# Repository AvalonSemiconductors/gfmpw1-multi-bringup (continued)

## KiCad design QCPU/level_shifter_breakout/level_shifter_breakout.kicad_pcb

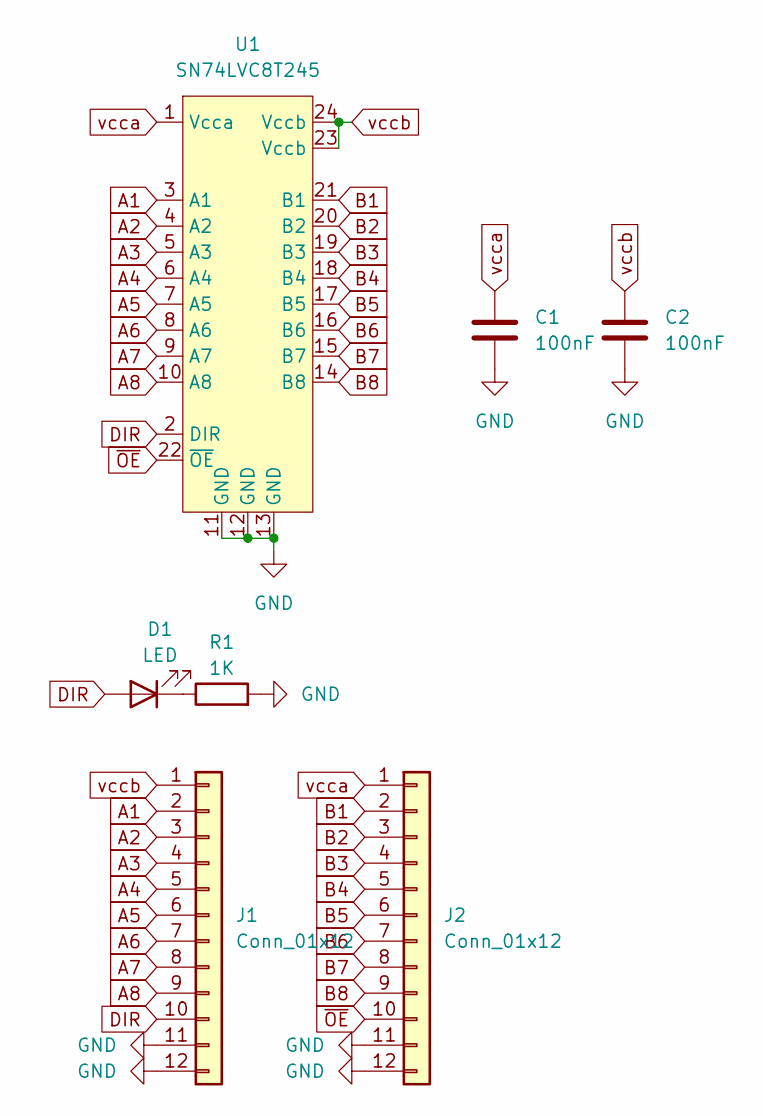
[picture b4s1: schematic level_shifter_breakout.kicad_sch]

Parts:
C1, C2: 100nF; C_0805_2012Metric_Pad1.18x1.45mm_HandSolder
D1: LED; LED_1206_3216Metric_Pad1.42x1.75mm_HandSolder
J1, J2: Conn_01x12; PinHeader_1x12_P2.54mm_Vertical
R1: 1K; R_2010_5025Metric_Pad1.40x2.65mm_HandSolder
U1: SN74LVC8T245; TSSOP-24_4.4x7.8mm_P0.65mm

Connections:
A1: J1.2, U1.3 (A1)
A2: J1.3, U1.4 (A2)
A3: J1.4, U1.5 (A3)
A4: J1.5, U1.6 (A4)
A5: J1.6, U1.7 (A5)
A6: J1.7, U1.8 (A6)
A7: J1.8, U1.9 (A7)
A8: J1.9, U1.10 (A8)
B1: J2.2, U1.21 (B1)
B2: J2.3, U1.20 (B2)
B3: J2.4, U1.19 (B3)
B4: J2.5, U1.18 (B4)
B5: J2.6, U1.17 (B5)
B6: J2.7, U1.16 (B6)
B7: J2.8, U1.15 (B7)
B8: J2.9, U1.14 (B8)
DIR: D1.2 (A), J1.10, U1.2 (DIR)
GND: C1.2, C2.2, J1.11, J1.12, J2.11, J2.12, R1.2, U1.11 (GND), U1.12 (GND), U1.13 (GND)
unnamed: D1.1 (K), R1.1
vcca: C1.1, J2.1, U1.1 (Vcca)
vccb: C2.1, J1.1, U1.23 (Vccb), U1.24 (Vccb)
~OE: J2.10, U1.22 (~OE)

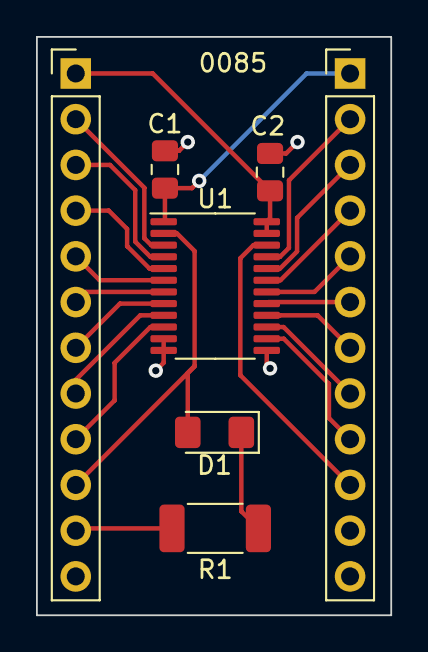
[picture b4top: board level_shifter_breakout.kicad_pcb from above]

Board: 2 copper layers, 19.7 x 32.1 mm, 7 parts (0 on the bottom side), 22 nets.

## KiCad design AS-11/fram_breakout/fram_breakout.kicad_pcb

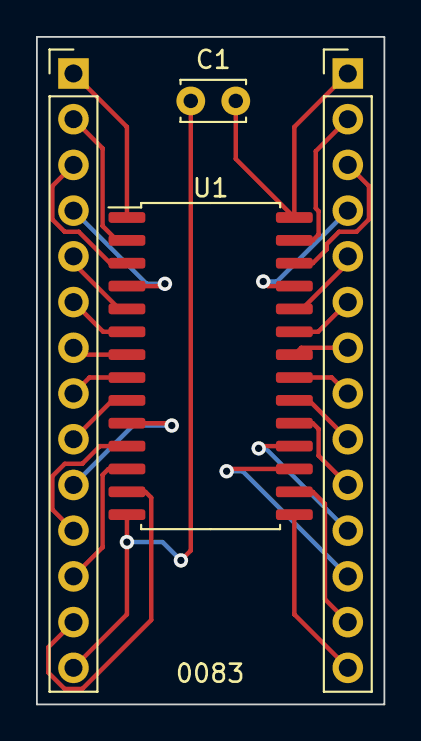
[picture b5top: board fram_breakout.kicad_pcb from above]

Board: 2 copper layers, 19.3 x 37.1 mm, 4 parts (0 on the bottom side), 28 nets.

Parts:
C1: 100nF; C_Disc_D3.4mm_W2.1mm_P2.50mm
J1, J2: Conn_01x14; PinHeader_1x14_P2.54mm_Vertical
U1: FM18W08-SG; SOIC-28W_7.5x17.9mm_P1.27mm

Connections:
A0: J2.10, U1.10 (A0)
A1: J2.9, U1.9 (A1)
A2: J2.8, U1.8 (A2)
A3: J2.7, U1.7 (A3)
A4: J2.6, U1.6 (A4)
A5: J2.5, U1.5 (A5)
A6: J2.4, U1.4 (A6)
A7: J2.3, U1.3 (A7)
A8: J1.4, U1.25 (A8)
A9: J1.5, U1.24 (A9)
A10: J1.8, U1.21 (A10)
A11: J1.6, U1.23 (A11)
A12: J2.2, U1.2 (A12)
A13: J1.3, U1.26 (A13)
A14: J2.1, U1.1 (A14)
DQ0: J2.11, U1.11 (DQ0)
DQ1: J2.12, U1.12 (DQ1)
DQ2: J2.13, U1.13 (DQ2)
DQ3: J1.14, U1.15 (DQ3)
DQ4: J1.13, U1.16 (DQ4)
DQ5: J1.12, U1.17 (DQ5)
DQ6: J1.11, U1.18 (DQ6)
DQ7: J1.10, U1.19 (DQ7)
unnamed: C1.2, J1.1, U1.28 (VDD)
unnamed: C1.1, J2.14, U1.14 (VSS)
~CE: J1.9, U1.20 (~CE)
~OE: J1.7, U1.22 (~OE)
~WE: J1.2, U1.27 (~WE)

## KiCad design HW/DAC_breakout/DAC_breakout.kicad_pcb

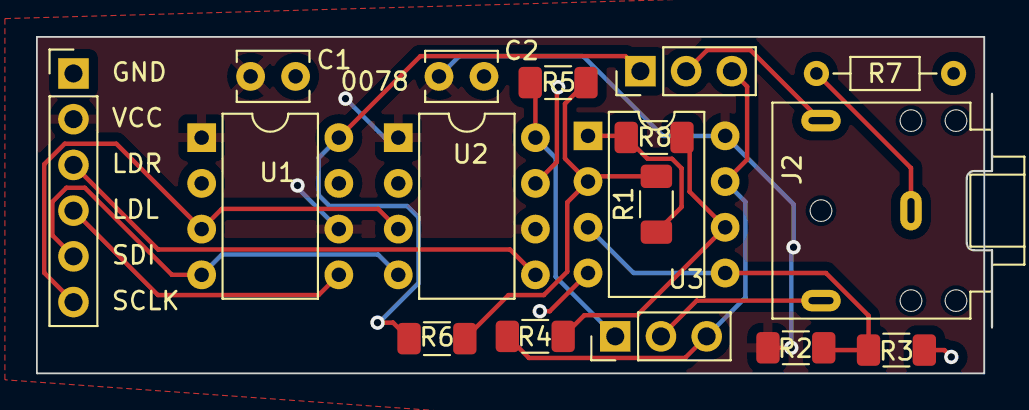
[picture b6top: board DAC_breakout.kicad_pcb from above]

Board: 2 copper layers, 53.1 x 18.7 mm, 17 parts (0 on the bottom side), 16 nets.

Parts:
C1, C2: 100nF; C_Disc_D3.8mm_W2.6mm_P2.50mm
J1: Conn_01x06; PinHeader_1x06_P2.54mm_Vertical
J2: AudioJack3; Jack_3.5mm_CUI_SJ1-3523N_Horizontal
J3, J4: Conn_01x03; PinHeader_1x03_P2.54mm_Vertical
R1, R2, R3, R4, R5, R6, R8: 10K; R_1206_3216Metric_Pad1.30x1.75mm_HandSolder
R7: 1K; R_Axial_DIN0204_L3.6mm_D1.6mm_P7.62mm_Horizontal
U1, U2: DAC7611; DIP-8_W7.62mm
U3: LM358; DIP-8_W7.62mm

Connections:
GND: C1.2, C2.2, J1.1, R3.2, R7.2, U1.2 (~CS), U1.7 (GND), U2.2 (~CS), U2.7 (GND), U3.4 (V-)
unnamed: J1.3, U2.5 (~LD)
unnamed: J1.4, U1.5 (~LD)
unnamed: J1.5, U1.4 (SDI), U2.4 (SDI)
unnamed: J1.6, U1.3 (CLK), U2.3 (CLK)
unnamed: J2.S, R7.1
unnamed: J3.1, R6.2, U1.8 (Vout)
unnamed: J2.T, J3.2
unnamed: J3.3, J4.3, R4.1, U3.7
unnamed: J4.1, R5.2, U2.8 (Vout)
unnamed: J2.R, J4.2
unnamed: R1.1, R8.2, U3.1
unnamed: R2.2, R3.1, U3.3 (+), U3.5 (+)
unnamed: R1.2, R5.1, R6.1, U3.2 (-)
unnamed: R4.2, R8.1, U3.6 (-)
VCC: C1.1, C2.1, J1.2, R2.1, U1.1 (Vdd), U1.6 (~CLR), U2.1 (Vdd), U2.6 (~CLR), U3.8 (V+)

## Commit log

2024-05-23 Hardware designs.
2024-08-04 Re-organize repo and start bringing things up!
2024-08-10 That should be all
2024-08-19 QCPU eval board PCB design
2024-08-20 Bug reports
2024-10-21 Minor tweaks, make QCPU work
2024-10-27 Caravel benchmark, RV makefile changes.
2024-11-28 Improvements in RISC-V and AS-11 softwares.
2024-11-28 Remove old files
2024-11-28 Remove more unneeded files.
2025-03-09 Trying to use caravel as a microcontroller
2025-03-16 Updated PSG stream code
2025-03-16 This is not supposed to be here
2025-04-29 AS-11: Memory monitor
2025-04-29 This is not supposed to be here....again
2025-04-29 RISC-V: Ethernet network stack progress.
2025-06-15 RISC-V network stack progress
2025-10-03 RISCV: TCP support in network stack.
2025-10-08 HTTP Server done
